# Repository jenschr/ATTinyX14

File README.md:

# ATTinyX14 development board
Tiny breadboard compatible development board that can contain either an ATTiny414, ATTiny814 or ATTiny1614 - depending on your need for Flash memory. This repo contains the complete Kicad design files under an MIT license as well as documentation, pinout & images of the verified design. I'm a consultant based in Oslo/Norway, so [get in touch](https://maketronics.no/about/) if you need custom hardware based on ATTiny or [other MCUs](https://flashgamer.com/blog/comments/microcontroller-reference-boards).

## Features
This nifty little microcontroller paired with the CH340 serial chip, makes for a very compact development board. Due to it's tiny size, you have 3 rows on each side of the breadboard to connect jumper wires to. When used with Spence Konde's brilliant [megaTinyCore](https://github.com/SpenceKonde/megaTinyCore), this is very smooth to use for prototyping.

The board has a builtin LED on (PA5) and a button (PA4) for testing. The Serial chip has a LED on the TX line, so you can visually inspect when programming is done and finished. My primary reason for looking at this chip series was the 8-bit DAC output on PA6. Very few MCU's in this price range has a builtin DAC, so it is very handy for many types projects such as controlling devices based on voltage. One such example is controlling 0-10V motors/fans by just adding a small OpAmp circuit.

Some things to note:

### 2-in-one
The UPDI programmer can be cut away, so you can use the MCU and programmer separately. In that case, the MCU must be powered separately, since the 3.3V regulator sits on the UPDI Programmer.

### Drawbacks
One drawback is that the setup does not allow for direct Serial debugging. You have to connect a separate Serial Converter/Adapter ([like this one](https://www.taydaelectronics.com/cp2102-serial-converter-usb-2-0-to-ttl-uart-ftdi.html) or anything similar) to use Arduino's Serial.

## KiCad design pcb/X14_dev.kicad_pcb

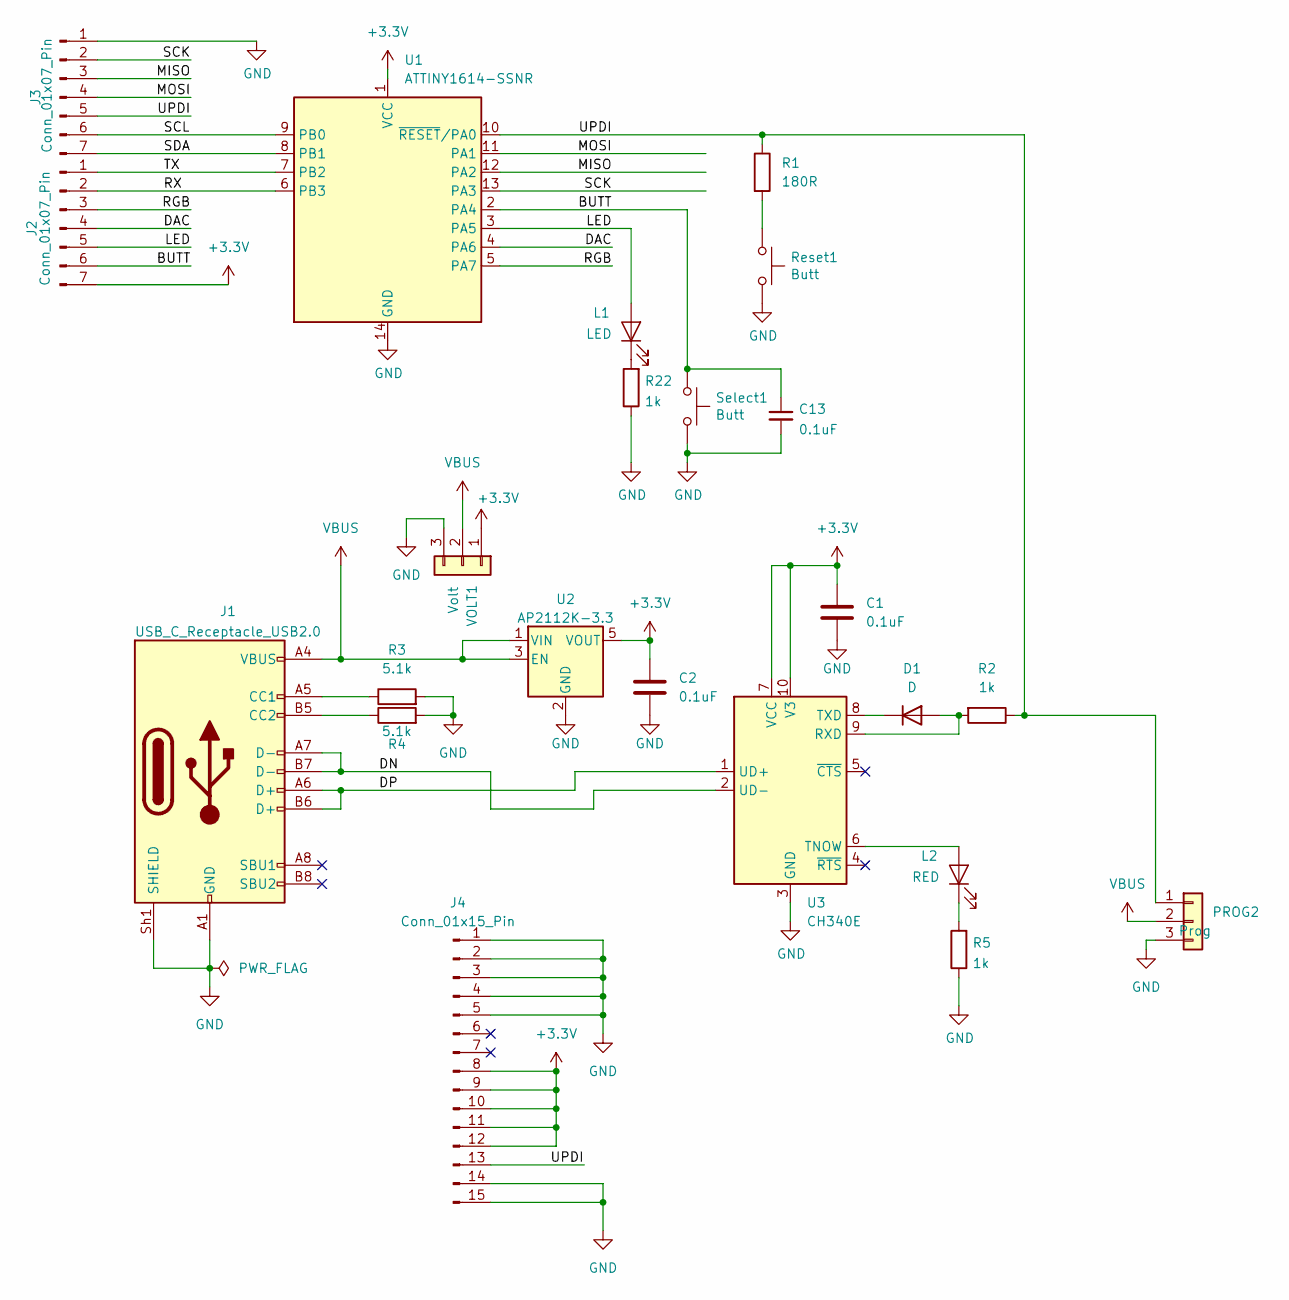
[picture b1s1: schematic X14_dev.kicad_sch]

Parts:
C1, C2: 0.1uF; C_0402_1005Metric; MPN CL05B104KA5NNNC
C13: 0.1uF; C_0402_1005Metric
D1: D; D_SOD-123
J1: USB_C_Receptacle_USB2.0; TYPE-C-31-M-14; MPN TYPE-C-31-M-14; LCSC Part # C223907
J2, J3: Conn_01x07_Pin; PinHeader_1x07_P2.54mm_Vertical
J4: Conn_01x15_Pin; PinHeader_1x16_P1.00mm_Vertical
L1: LED; LED_0402_1005Metric
L2: RED; LED_0402_1005Metric
PROG2: Prog; PinHeader_1x03_P2.54mm_Vertical
R1: 180R; R_0402_1005Metric
R2, R5, R22: 1k; R_0402_1005Metric
R3, R4: 5.1k; R_0402_1005Metric
Reset1: Butt; TS-1088-AR02016; MPN TS-1088-AR02016; LCSC C720477
Select1: Butt; TS-1088-AR02016; MPN TS-1088-AR02016; LCSC C720477
U1: ATTINY1614-SSNR; SOIC-14_3.9x8.7mm_P1.27mm; MPN ATTINY1614-SSNR; LCSC C481364
U2: AP2112K-3.3; SOT-23-5; MPN AP2112K-3.3TRG1
U3: CH340E; MSOP-10_3x3mm_P0.5mm
VOLT1: Volt; PinHeader_1x03_P2.54mm_Vertical

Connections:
+3.3V: C1.2, C2.2, J2.7, J4.8, J4.9, J4.10, J4.11, J4.12, U1.1 (VCC), U2.5 (VOUT), U3.7 (VCC), U3.10 (V3), VOLT1.1
/BUTT: C13.1, J2.6, Select1.1, U1.2 (PA4)
/DAC: J2.4, U1.4 (PA6)
/DN: J1.A7 (D-), J1.B7 (D-), U3.2 (UD-)
/DP: J1.A6 (D+), J1.B6 (D+), U3.1 (UD+)
/LED: J2.5, L1.2 (A), U1.3 (PA5)
/MISO: J3.3, U1.12 (PA2)
/MOSI: J3.4, U1.11 (PA1)
/RGB: J2.3, U1.5 (PA7)
/RX: J2.2, U1.6 (PB3)
/SCK: J3.2, U1.13 (PA3)
/SCL: J3.6, U1.9 (PB0)
/SDA: J3.7, U1.8 (PB1)
/TX: J2.1, U1.7 (PB2)
/UPDI: J3.5, J4.13, PROG2.1, R1.1, R2.1, U1.10 (~RESET/PA0)
GND: C1.1, C2.1, C13.2, J1.A1 (GND), J1.A12 (GND), J1.B1 (GND), J1.B12 (GND), J1.Sh1 (SHIELD), J3.1, J4.1, J4.2, J4.3, J4.4, J4.5, J4.14, J4.15, PROG2.3, R3.2, R4.2, R5.1, R22.1, Reset1.2, Select1.2, U1.14 (GND), U2.2 (GND), U3.3 (GND), VOLT1.3
unnamed: D1.2 (A), R2.2, U3.9 (RXD)
unnamed: D1.1 (K), U3.8 (TXD)
unnamed: J1.A5 (CC1), R3.1
unnamed: J1.B5 (CC2), R4.1
unnamed: L1.1 (K), R22.2
unnamed: L2.2 (A), U3.6 (TNOW)
unnamed: L2.1 (K), R5.2
unnamed: R1.2, Reset1.1
VBUS: J1.A4 (VBUS), J1.A9 (VBUS), J1.B4 (VBUS), J1.B9 (VBUS), PROG2.2, U2.1 (VIN), U2.3 (EN), VOLT1.2

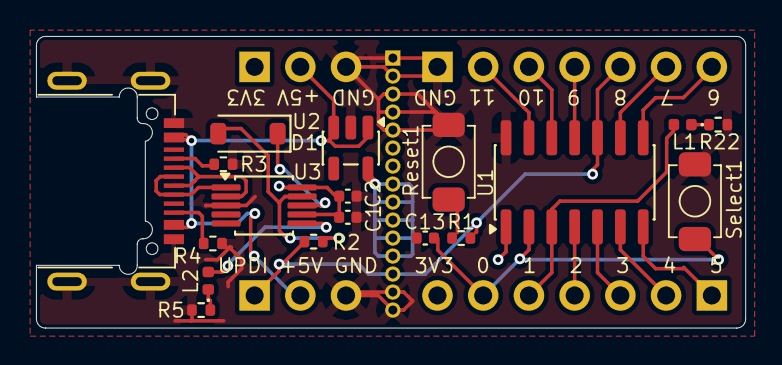
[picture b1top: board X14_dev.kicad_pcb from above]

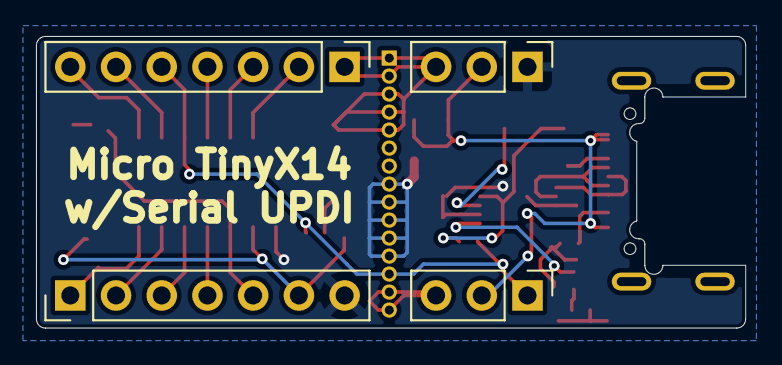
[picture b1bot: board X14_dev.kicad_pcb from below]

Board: 2 copper layers, 39.4 x 16.2 mm, 23 parts (4 on the bottom side), 25 nets.

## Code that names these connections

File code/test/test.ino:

/*
 * Basic test-sketch for button and LED on x14 devboard
 */


#define PA4 0  // SS/A4/Button
#define PA5 1  // A5/LED
#define PA6 2  // A6/DAC
#define PA7 3  // A7
#define PB3 4  // RX
#define PB2 5  // TX
#define PB1 6  // SDA/A10
#define PB0 7  // SCL/A11
#define PA1 8  // MOSI/TX1/A1
#define PA2 9  // MISO/RX1/A2
#define PA3 10 // SCK/A3
#define PA0 11 // UPDI programming

int count = 0;
bool wasButtonPressed = false;

void setup() {
  Serial.begin(9600);
  delay(4000);
  Serial.println("test");
  pinMode(PA5, OUTPUT);       // LED
  pinMode(PA4, INPUT_PULLUP); // Button
}

void loop() {
  // If button is pressed, keep LED turned on
  bool isButtonPressed = !digitalRead(PA4);
  if( isButtonPressed != wasButtonPressed ){
    Serial.println( isButtonPressed );
    digitalWrite( PA5, isButtonPressed );
    delay(100);// simple debounce
  }
  wasButtonPressed = isButtonPressed;

  // Toggle LED every 10000 loops
  if( !isButtonPressed && count % 10000 == 0 ){
    digitalWrite( PA5, !digitalRead(PA5) );
  } else if( isButtonPressed ){
    analogWrite( PA5, (count % 255) );
    delay(3);
  }
  count++;
}

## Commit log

2026-05-19 First public version
2026-05-19 Link correct repo
2026-05-19 More info
2026-05-19 Even more info
2026-05-19 Updated title
2026-05-19 Typo
